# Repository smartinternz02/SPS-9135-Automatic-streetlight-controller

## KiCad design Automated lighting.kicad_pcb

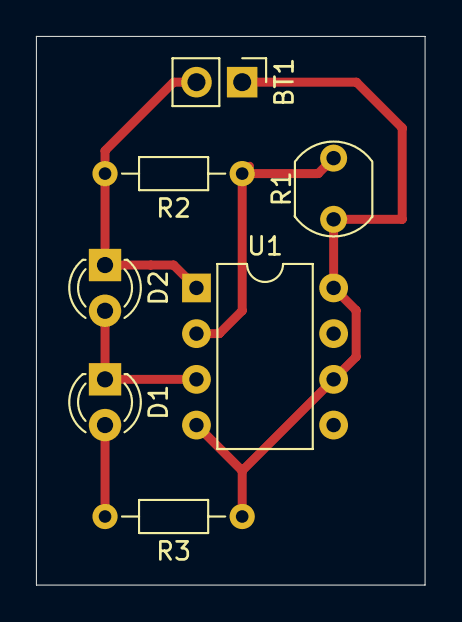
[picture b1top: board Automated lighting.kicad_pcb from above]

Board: 2 copper layers, 21.6 x 30.5 mm, 7 parts (0 on the bottom side), 5 nets.

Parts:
BT1: 9V; PinHeader_1x02_P2.54mm_Vertical
D1, D2: LED; LED_D3.0mm
R1: LDR07; R_LDR_5.1x4.3mm_P3.4mm_Vertical
R2: 47K; R_Axial_DIN0204_L3.6mm_D1.6mm_P7.62mm_Horizontal
R3: 330E; R_Axial_DIN0204_L3.6mm_D1.6mm_P7.62mm_Horizontal
U1: NE555P; DIP-8_W7.62mm

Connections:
GND: BT1.2, D2.1, R2.2, U1.1
unnamed: BT1.1, R1.1, R3.1, U1.4, U1.6, U1.8
unnamed: D1.1, D2.2, U1.3
unnamed: D1.2, R3.2
unnamed: R1.2, R2.1, U1.2

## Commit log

2021-03-24 Create final video link
